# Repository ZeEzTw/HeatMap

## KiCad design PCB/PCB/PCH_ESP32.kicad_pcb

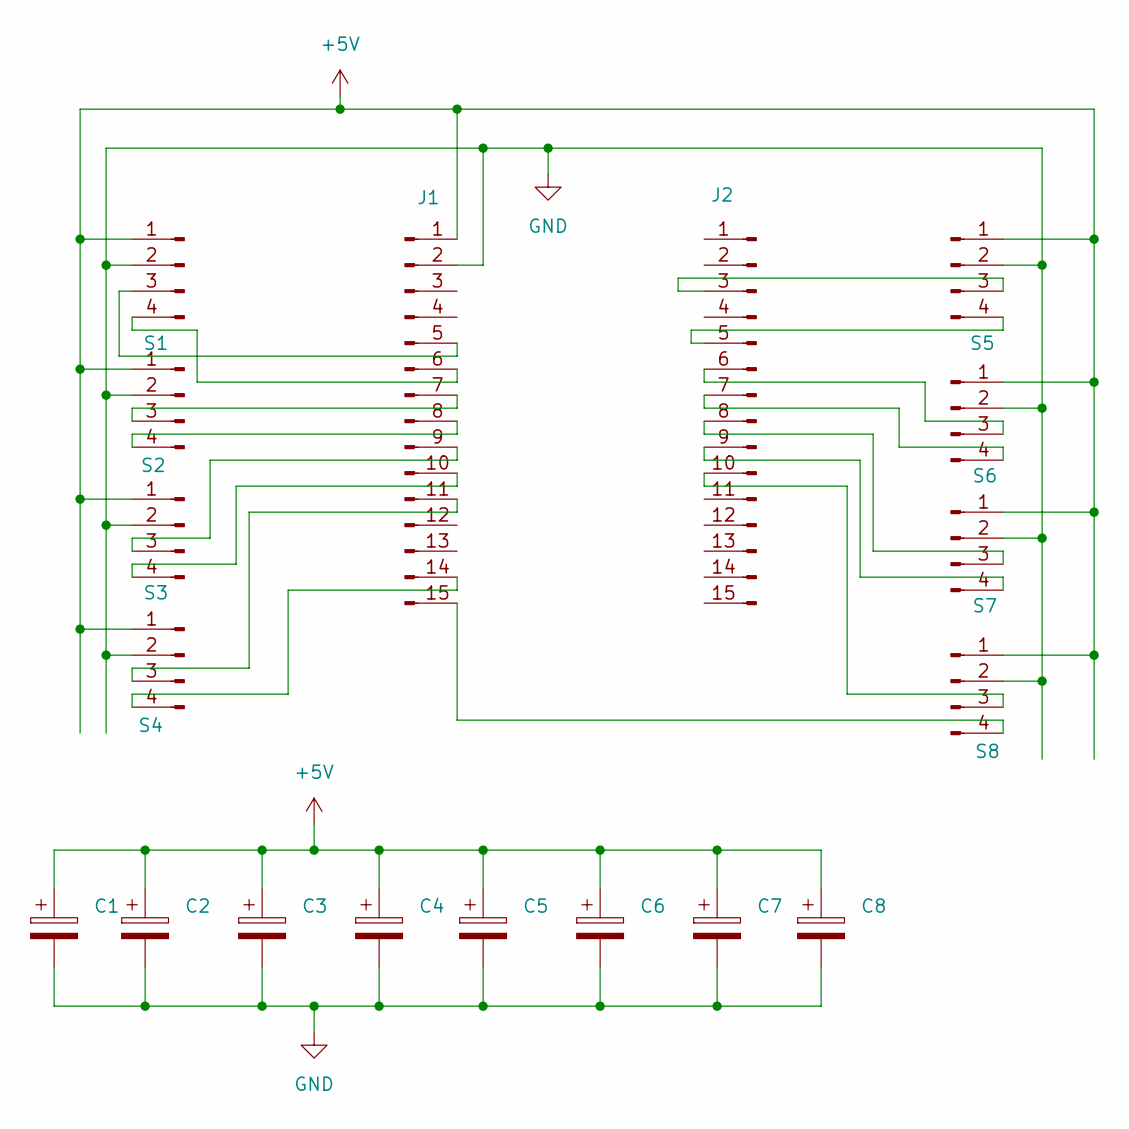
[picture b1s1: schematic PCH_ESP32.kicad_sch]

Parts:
C1, C2, C3, C4, C5, C6, C7, C8: C_Polarized; C_0805_2012Metric
J1, J2: Conn_01x16_Pin; PinHeader_1x15_P2.54mm_Vertical
S1, S2, S3, S4, S5, S6, S7, S8: Conn_01x04_Pin; PinHeader_1x04_P2.54mm_Vertical

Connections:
+5V: C1.1, C2.1, C3.1, C4.1, C5.1, C6.1, C7.1, C8.1, J1.1, S1.1, S2.1, S3.1, S4.1, S5.1, S6.1, S7.1, S8.1
GND: C1.2, C2.2, C3.2, C4.2, C5.2, C6.2, C7.2, C8.2, J1.2, S1.2, S2.2, S3.2, S4.2, S5.2, S6.2, S7.2, S8.2
unnamed: J1.5, S1.3
unnamed: J1.6, S1.4
unnamed: J1.7, S2.3
unnamed: J1.8, S2.4
unnamed: J1.9, S3.3
unnamed: J1.10, S3.4
unnamed: J1.11, S4.3
unnamed: J1.14, S4.4
unnamed: J1.15, S8.4
unnamed: J2.5, S5.4
unnamed: J2.7, S6.4
unnamed: J2.3, S5.3
unnamed: J2.8, S7.3
unnamed: J2.10, S8.3
unnamed: J2.9, S7.4
unnamed: J2.6, S6.3

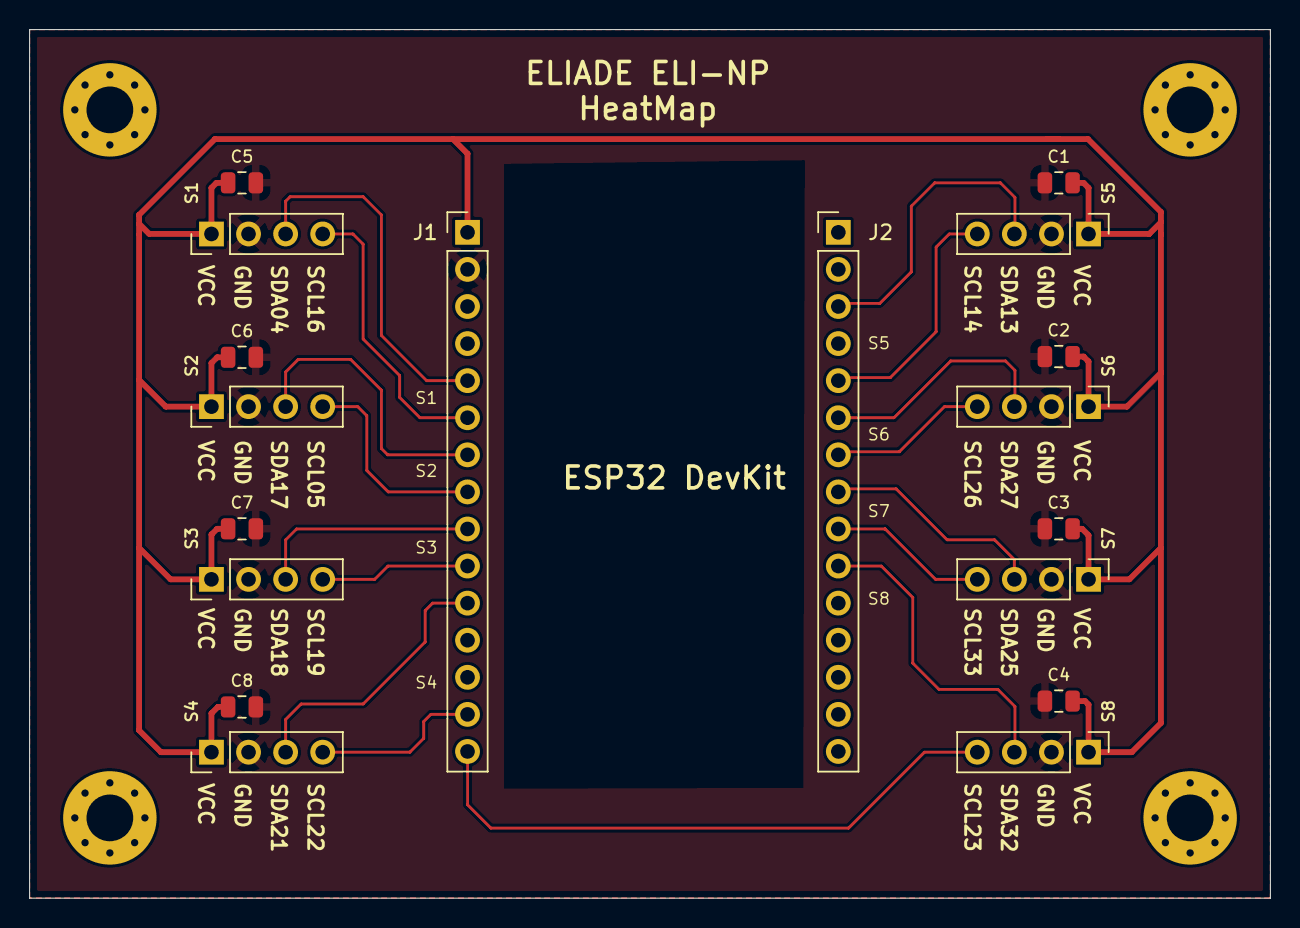
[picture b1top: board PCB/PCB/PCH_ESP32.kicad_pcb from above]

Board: 2 copper layers, 85.0 x 59.5 mm, 18 parts (0 on the bottom side), 18 nets.

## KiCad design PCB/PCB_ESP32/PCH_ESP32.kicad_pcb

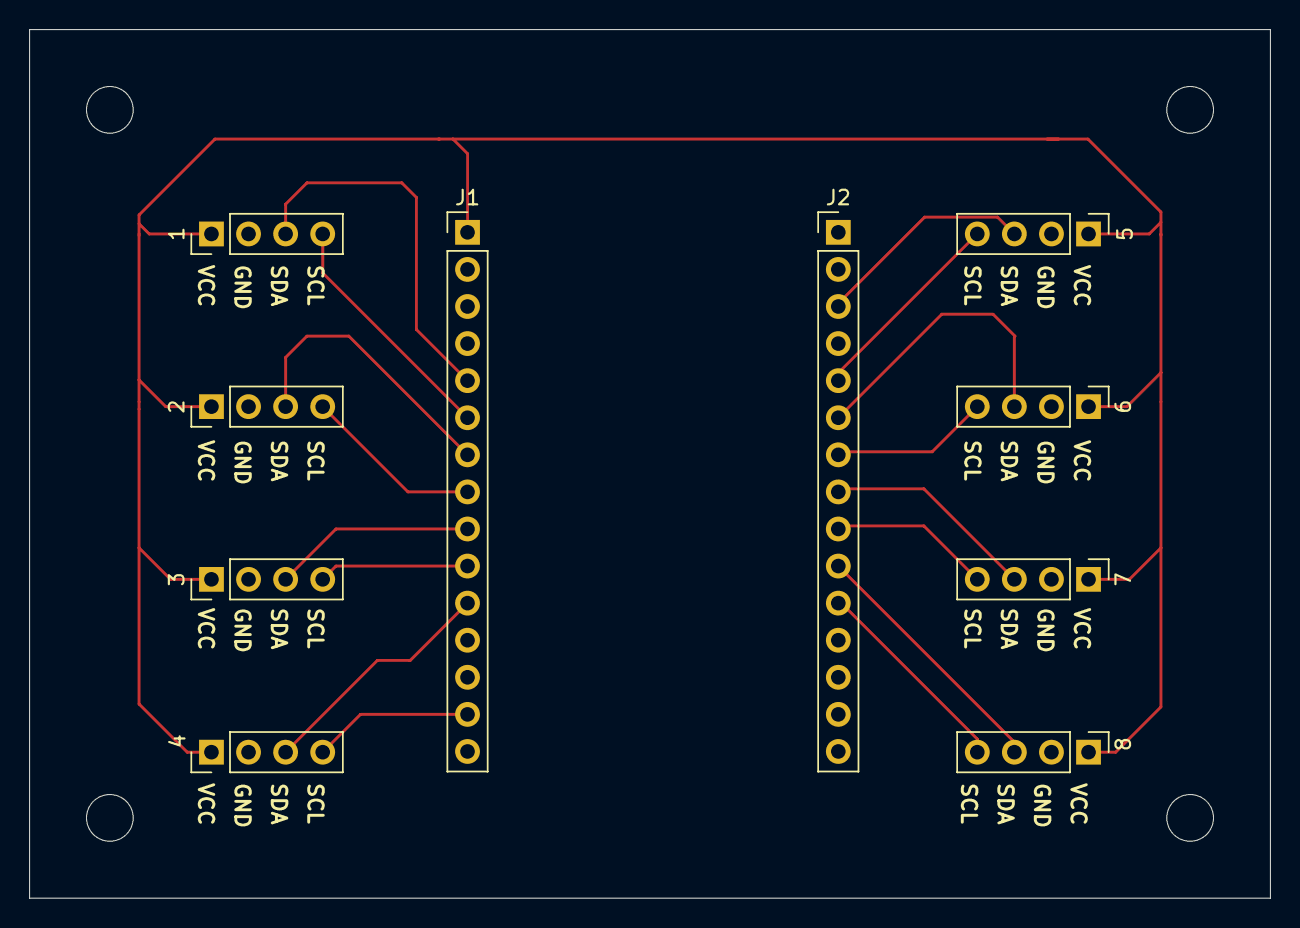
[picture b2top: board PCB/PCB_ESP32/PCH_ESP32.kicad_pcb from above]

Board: 2 copper layers, 85.0 x 59.5 mm, 10 parts (0 on the bottom side), 18 nets.

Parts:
1, 2, 3, 4, 5, 6, 7, 8: Conn_01x04_Pin; PinHeader_1x04_P2.54mm_Vertical
J1, J2: Conn_01x16_Pin; PinHeader_1x15_P2.54mm_Vertical

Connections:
unnamed: 1.1, 2.1, 3.1, 4.1, 5.1, 6.1, 7.1, 8.1, J1.1
unnamed: 1.2, 2.2, 3.2, 4.2, 5.2, 6.2, 7.2, 8.2, J1.2
unnamed: 1.3, J1.5
unnamed: 1.4, J1.6
unnamed: 2.3, J1.7
unnamed: 2.4, J1.8
unnamed: 3.3, J1.9
unnamed: 3.4, J1.10
unnamed: 4.3, J1.11
unnamed: 4.4, J1.14
unnamed: 5.3, J2.3
unnamed: 5.4, J2.5
unnamed: 6.3, J2.6
unnamed: 6.4, J2.7
unnamed: 7.3, J2.8
unnamed: 7.4, J2.9
unnamed: 8.3, J2.10
unnamed: 8.4, J2.11

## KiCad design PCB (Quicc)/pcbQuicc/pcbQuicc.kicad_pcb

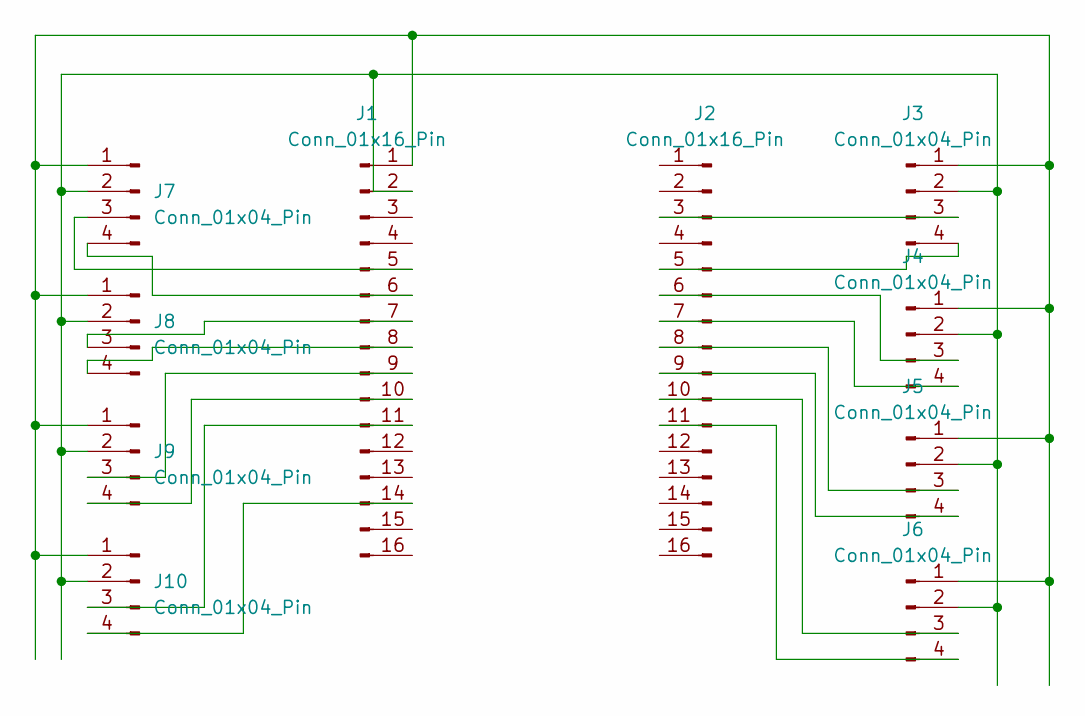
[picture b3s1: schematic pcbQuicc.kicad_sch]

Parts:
J1, J2: Conn_01x16_Pin; PinHeader_1x15_P2.54mm_Vertical
J3, J4, J5, J6, J7, J8, J9: Conn_01x04_Pin; JST_SH_BM04B-SRSS-TB_1x04-1MP_P1.00mm_Vertical
J10: Conn_01x04_Pin; PinHeader_1x04_P2.54mm_Vertical

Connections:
unnamed: J1.2 (GND), J3.2, J4.2, J5.2, J6.2, J7.2 (GND), J8.2 (GND), J9.2, J10.2
unnamed: J1.1, J3.1, J4.1, J5.1, J6.1, J7.1, J8.1, J9.1, J10.1
unnamed: J1.5, J7.3
unnamed: J1.6, J7.4
unnamed: J1.7, J8.3
unnamed: J1.8, J8.4
unnamed: J1.9, J9.3
unnamed: J1.10, J9.4
unnamed: J1.11, J10.3
unnamed: J1.14, J10.4
unnamed: J2.3, J3.3
unnamed: J2.5, J3.4
unnamed: J2.6, J4.3
unnamed: J2.7, J4.4
unnamed: J2.8, J5.3
unnamed: J2.9, J5.4
unnamed: J2.10, J6.3
unnamed: J2.11, J6.4

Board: 2 copper layers, 10 parts (0 on the bottom side), 18 nets, no tracks yet.

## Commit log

2025-06-23 ProjectPrezentationIdea
2025-06-23 Initial ESP32 + AHT21 integration: data read, Wi-Fi, and InfluxDB write
    - Received ESP32 board with 2 AHT21 sensors
    - Configured device for Linux detection
    - Wrote prototype code to read and print temperature/humidity values
    - Verified sensor data accuracy
    - Added Wi-Fi connection and live InfluxDB cloud integration
    Next: -test 2 sensors with Qwiic conncetion
2025-06-24 Added JSON-based configuration system for ESP32 device Device now reads key parameters (Wi-Fi, InfluxDB, ID, delay) from a JSON file stored with the firmware Implemented NTP-based time synchronizatio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
    Next: -test 2 sensors with Qwiic conncetion
    -design project flow (pdf)
2025-07-02 save commit
2025-07-04 added v2 of the code, where I tried to bitBang pins to use them as I2C, i managed to call the sensor and recive some data, but somthing its wrong
2025-07-04 Added support for all sensors, I siwtch the declaration of the TwoWire and initialize it with each bin pair, and then kill it, and do this in a loop, after taking the data
2025-07-17 am adaugat error si o suma pentru date mai bune
2025-07-21 am adaugat planul de achizitie si o reprezentare a proiectului + cateva modificari la cod cu medie
2025-07-22 added the minimum delay between reading and multiple readings
2025-08-19 added a new version of the code, with the v1 of the pcb
2025-08-20 Added a debug version to test the stop reasons.
2025-08-21 implemetet telegram messages for debbuging
2025-08-28 added the stl file for 3d printing test
2025-09-04 new code version with advanced debuging
2025-09-17 Added a new organized version of the final code, with better format and improved debugging
2025-09-17 added PCB schematic
2025-09-17 changed the delay for senzors reding + more info to telegram messages, to show which senzor is failing
2025-10-14 Tried using SoftWire without success. Created a new library, BitBandAht21Eli, that simulates I2C protocol on any GPIO, based on a specific class. Successfully initialized the sensor and read data usi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
2025-11-14 created bigbang for i2c conexion libraty
2025-11-20 removed Adafruit_AHTx0.h and Wire.h dependency
2025-11-20 removed Senzor.h and Senzor.cpp, ale the variables is now in Error.h
2025-11-20 added UseOfHeatMapSoftware.pdf as a guide to run the program
2025-11-20 removed some #include
2025-11-20 added a #include
2025-11-27 new config changes
2025-11-27 implemeneted InfluxDBLocal writting, for the final version of the code extra, removed the time syncornization, to avoid influxDB error for 2 eso writting in the same time
2025-12-09 new pcb model
2025-12-22 added the new pcb design, and fixel the code to write real values
2026-03-01 Box design v1 ipt
    The ipb for the box that will hold the pcb and the esp32
2026-05-10 Update sda/scl swap if wiring is wrong placed
2026-05-16 code update to expalin each reset error better
